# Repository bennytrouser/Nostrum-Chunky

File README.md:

# Nostrum-Chunky
An MX Spaced 32 key Split KB using Seeed Xiao BLE.

- Created with the [ergogen](https://github.com/ergogen/ergogen) and KiCad9. Case files created with Autodesk Fusion360.
- Footprints for both MX and Choc V2 switches (Currently case only for MX)
- Firmware using ZMK, including the RGB Widget module from [Caksoylar](https://github.com/caksoylar/zmk-rgbled-widget)
- Inspiration from the [Hummingbird](https://github.com/PJE66/hummingbird) style [Berylline](https://github.com/jcmkk3/trochilidae#berylline) by [jcmkk3](https://github.com/jcmkk3)

## PCB View
| Front | Back |
| ----- | ----- |
|  |  |

## Design
Iniitially I just wanted to make a simple MX version of the NostrumX, but this ended up with a new case design with a gasket mounted 3dp plate. I also removed the splay that I decided was not required with the extra spacing from the MX layout.

I tried various foam and plate options and settled on just 0.5mm ixpe switch pads and silicone gaskets on the plate. I tried a thinner plate which created more flex, but I hated the bouncy feedback, so I went with a 3mm plate, printed with 100% infill. This seems to have created a really great sound and typing feel with the switches I chose - Akko Mirrors, which convieniently match the case.

Note - Akko switches are usually a little smaller than most, so for other switches, make sure to use the loose version of the plates (these use a 13.97 hole rather than the 13.9 for the Akko).

The case is joins together with 3x2 magnets for easy disassembly and access to the hidden power switch when required.

There should be enough space for the larger 402030 lipo in both sides, but I used what I had available, and the right half uses far less power anyway.

### Lesson Learned
Unlike previous builds that relied almost entirely on Ergogen to create the PCB, this time I left all the nets blank in Ergogen and used a schematic in Kicad. But I made a mistake and accidentally assigned SOD-523 diodes instead of SOD-123. These are significantly smaller, so if you want to copy or take inspiration, I would highly recommend not using them! If in the unlikely event you want to order the board for yourself, do yourself a favour and swap to SOD-123 and re-route. Unless you like soldering with a digital microscope. See pic for scale next to SOD-123.

## Parts
| Part  | Link |
| ------------- | ------------- |
| Battery 402030 | https://www.ebay.co.uk/itm/355875616696 |
| Battery 401322 | https://www.ebay.co.uk/itm/195234785175 |
| SMD diodes SOD-523 1N4148W T4 | https://www.mouser.co.uk/ProductDetail/637-1N4148WT |
| 1.5mm Fibreoptic cable (for led shinethrough) | https://www.aliexpress.com/item/1005005886250822.html |
| Power switch PCM12 | https://www.aliexpress.com/item/32912838968.html |
| Feet 3x14x1.5mm | https://www.aliexpress.com/item/1005006691343859.html |
| Seeeduino Xiao nrf52840 (various vendors) | https://thepihut.com/products/seeed-xiao-ble-nrf52840 | 
| Gaskets | https://www.aliexpress.com/item/1005008463912507.html|
| IXPE switch pads (Various vendors link just an example) | https://www.amazon.co.uk/dp/B0D6VR14WD |
| Magnets 3x2mm (I got mine on Amazon) | https://www.amazon.co.uk/Magnet-Expert%C2%AE-3mm-thick-Neodymium/dp/B003BKPIN0/ref=sr_1_22 |

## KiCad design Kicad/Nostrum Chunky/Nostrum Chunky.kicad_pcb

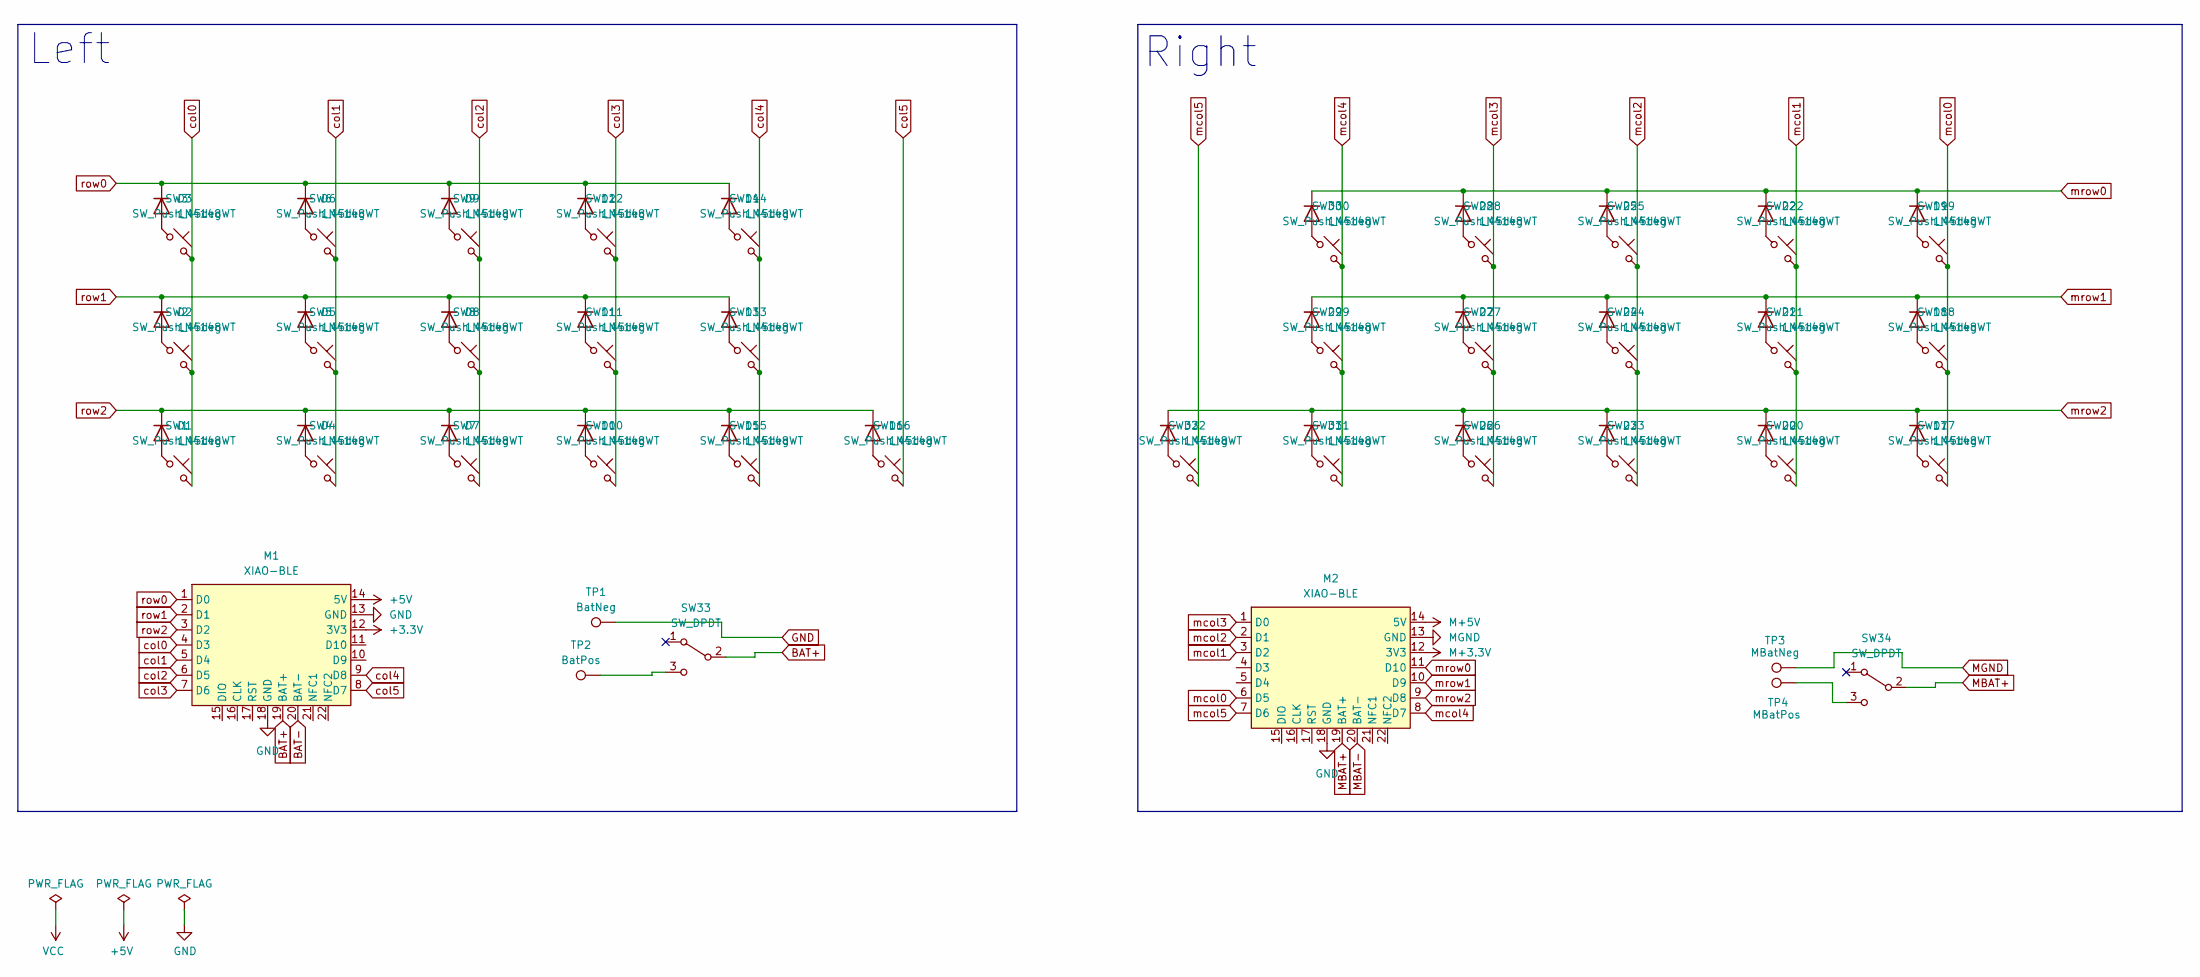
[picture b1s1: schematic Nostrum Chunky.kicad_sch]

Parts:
D1, D2, D3, D4, D5, D6, D7, D8, D9, D10, D11, D12, D13, D14, D15, D16, D17, D18, D19, D20, D21, D22, D23, D24, D25, D26, D27, D28, D29, D30, D31, D32: 1N4148WT; D_SOD-523
M1, M2: XIAO-BLE; xiao-ble-smd-batcut
SW1, SW2, SW3, SW4, SW5, SW6, SW7, SW8, SW9, SW10, SW11, SW12, SW13, SW14, SW15, SW16, SW17, SW18, SW19, SW20, SW21, SW22, SW23, SW24, SW25, SW26, SW27, SW28, SW29, SW30, SW31, SW32: SW_Push_45deg; Switch_MXChocV2_combo
SW33, SW34: SW_DPDT; SW_SPDT_PCM12; LCSC C431540
TP1: BatNeg; SMDPad
TP2: BatPos; SMDPad
TP3: MBatNeg; SMDPad
TP4: MBatPos; SMDPad

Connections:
+3.3V: M1.12 (3V3)
+5V: M1.14 (5V)
BAT+: M1.19 (BAT+), SW33.2 (B)
GND: M1.13 (GND), M1.18 (GND), M2.18 (GND), TP1.1
M+3.3V: M2.12 (3V3)
M+5V: M2.14 (5V)
MBAT+: M2.19 (BAT+), SW34.2 (B)
MGND: M2.13 (GND), TP3.1
unnamed: D1.2 (A), SW1.1
unnamed: D2.2 (A), SW2.1
unnamed: D3.2 (A), SW3.1
unnamed: D4.2 (A), SW4.1
unnamed: D5.2 (A), SW5.1
unnamed: D6.2 (A), SW6.1
unnamed: D7.2 (A), SW7.1
unnamed: D8.2 (A), SW8.1
unnamed: D9.2 (A), SW9.1
unnamed: D10.2 (A), SW10.1
unnamed: D11.2 (A), SW11.1
unnamed: D12.2 (A), SW12.1
unnamed: D13.2 (A), SW13.1
unnamed: D14.2 (A), SW14.1
unnamed: D15.2 (A), SW15.1
unnamed: D16.2 (A), SW16.1
unnamed: D17.2 (A), SW17.1
unnamed: D18.2 (A), SW18.1
unnamed: D19.2 (A), SW19.1
unnamed: D20.2 (A), SW20.1
unnamed: D21.2 (A), SW21.1
unnamed: D22.2 (A), SW22.1
unnamed: D23.2 (A), SW23.1
unnamed: D24.2 (A), SW24.1
unnamed: D25.2 (A), SW25.1
unnamed: D26.2 (A), SW26.1
unnamed: D27.2 (A), SW27.1
unnamed: D28.2 (A), SW28.1
unnamed: D29.2 (A), SW29.1
unnamed: D30.2 (A), SW30.1
unnamed: D31.2 (A), SW31.1
unnamed: D32.2 (A), SW32.1
unnamed: SW33.3 (C), TP2.1
unnamed: SW34.3 (C), TP4.1
col0: M1.4 (D3), SW1.2, SW2.2, SW3.2
col1: M1.5 (D4), SW4.2, SW5.2, SW6.2
col2: M1.6 (D5), SW7.2, SW8.2, SW9.2
col3: M1.7 (D6), SW10.2, SW11.2, SW12.2
col4: M1.9 (D8), SW13.2, SW14.2, SW15.2
col5: M1.8 (D7), SW16.2
mcol0: M2.6 (D5), SW17.2, SW18.2, SW19.2
mcol1: M2.3 (D2), SW20.2, SW21.2, SW22.2
mcol2: M2.2 (D1), SW23.2, SW24.2, SW25.2
mcol3: M2.1 (D0), SW26.2, SW27.2, SW28.2
mcol4: M2.8 (D7), SW29.2, SW30.2, SW31.2
mcol5: M2.7 (D6), SW32.2
mrow0: D19.1 (K), D22.1 (K), D25.1 (K), D28.1 (K), D30.1 (K), M2.11 (D10)
mrow1: D18.1 (K), D21.1 (K), D24.1 (K), D27.1 (K), D29.1 (K), M2.10 (D9)
mrow2: D17.1 (K), D20.1 (K), D23.1 (K), D26.1 (K), D31.1 (K), D32.1 (K), M2.9 (D8)
row0: D3.1 (K), D6.1 (K), D9.1 (K), D12.1 (K), D14.1 (K), M1.1 (D0)
row1: D2.1 (K), D5.1 (K), D8.1 (K), D11.1 (K), D13.1 (K), M1.2 (D1)
row2: D1.1 (K), D4.1 (K), D7.1 (K), D10.1 (K), D15.1 (K), D16.1 (K), M1.3 (D2)

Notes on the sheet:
Right
Left

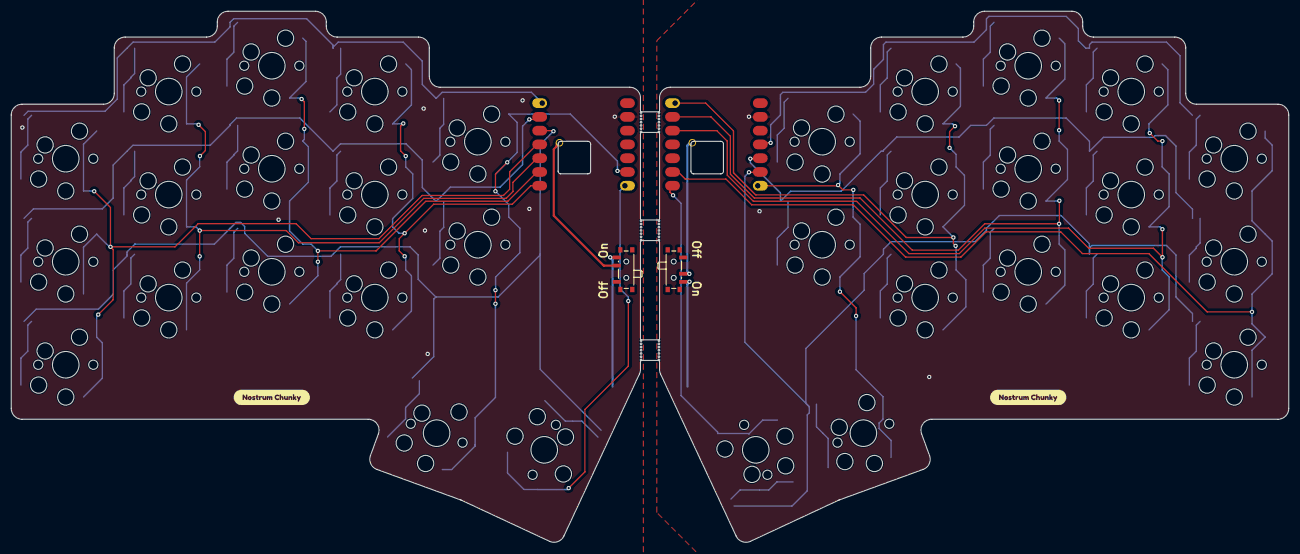
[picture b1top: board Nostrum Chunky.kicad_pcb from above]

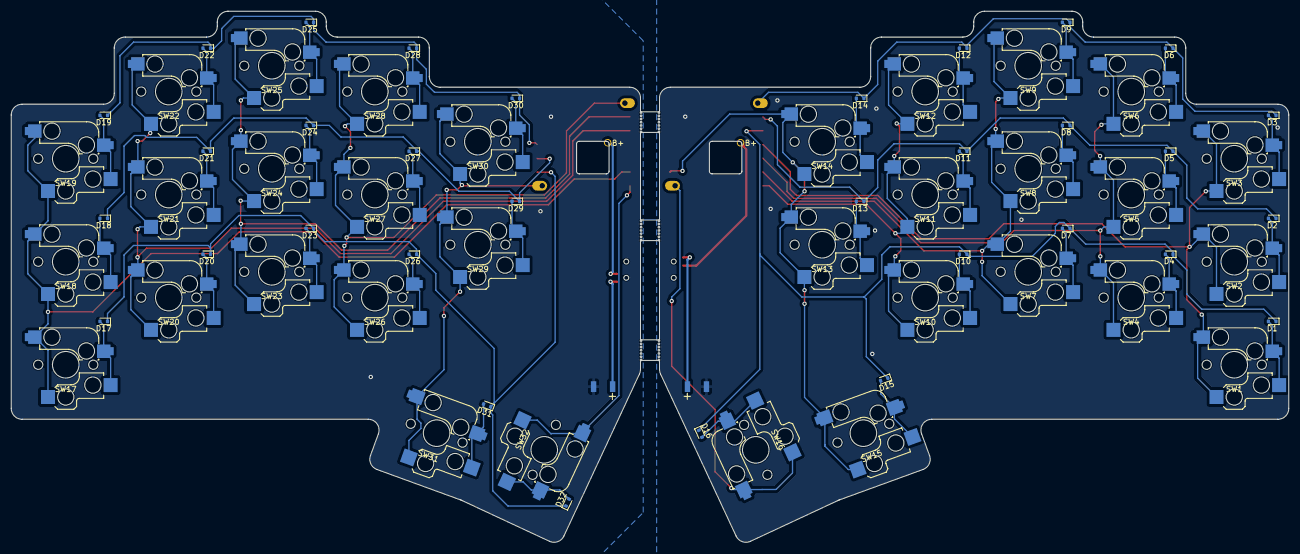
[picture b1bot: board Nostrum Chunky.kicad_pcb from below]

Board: 2 copper layers, 235.6 x 97.9 mm, 80 parts (32 on the bottom side), 56 nets.

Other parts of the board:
H7, H7#2, H7#3, H7#4, H7#5, H7#6: Breakaway Tabs; Breakaway_Tabs_Med
kibuzzard-67FBD43F, kibuzzard-67FBD43F#2: G***; kibuzzard-67FBD43F

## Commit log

2025-04-28 initial upload
2025-04-28 readme update
2025-04-28 Readme edit
2025-05-03 Added loose plates and updated readme with note on plate fitment
